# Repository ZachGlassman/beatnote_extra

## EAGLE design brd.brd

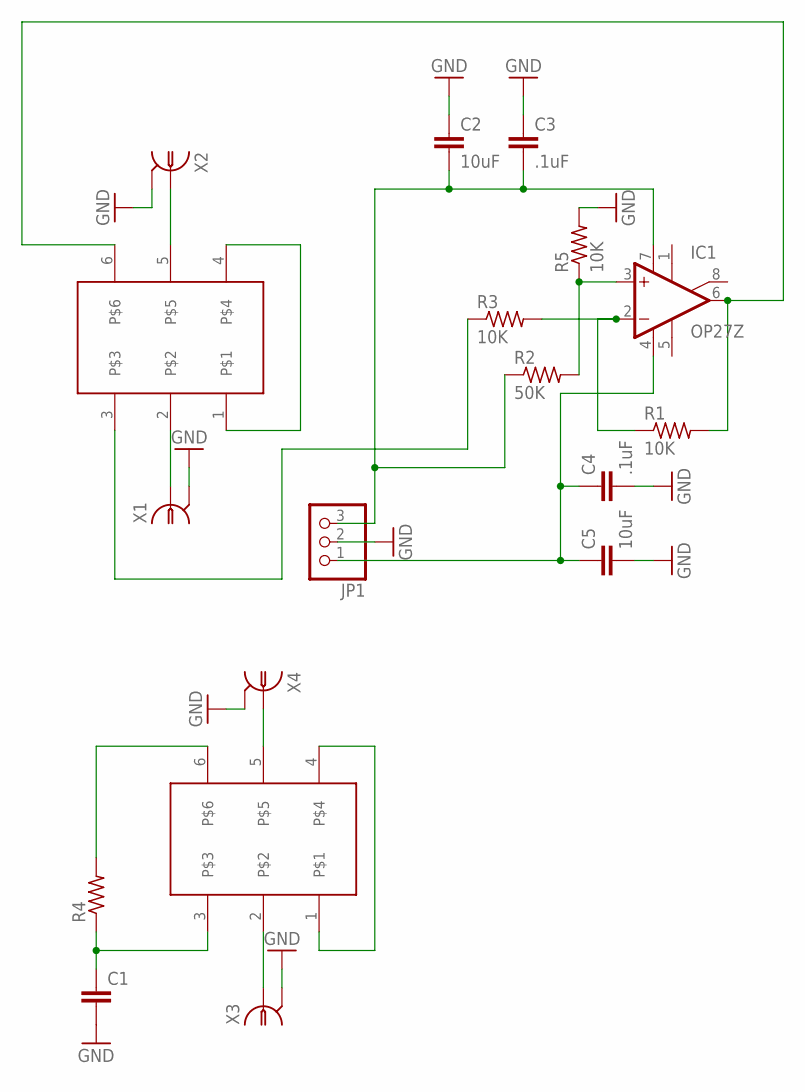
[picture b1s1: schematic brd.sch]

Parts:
C1: C-EU025-024X044; C025-024X044
C2, C5: 10uF; C025-024X044
C3, C4: .1uF; C025-024X044
IC1: OP27Z; DIL08
JP1: PINHD-1X3; 1X03
R1, R3, R5: 10K; 0204V
R2: 50K; 0204V
R4: R-US_0204/2V; 0204V
U$1, U$2: DP3T-TOGGLE; 7201MD9AV2BE
X1, X2, X3, X4: BNC-H; BNC90

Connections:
GND: C1.2, C2.1, C3.1, C4.2, C5.2, JP1.2, R5.2, X1.2, X2.2, X3.2, X4.2
unnamed: IC1.2 (-IN), R1.1, R3.2
unnamed: IC1.6 (OUT), R1.2, U$1.6
unnamed: C4.1, C5.1, IC1.4 (V-), JP1.1
unnamed: U$2.2, X3.1
unnamed: U$2.5, X4.1
unnamed: U$1.2, X1.1
unnamed: C2.2, C3.2, IC1.7 (V+), JP1.3, R2.1
unnamed: C1.1, R4.1, U$2.3
unnamed: IC1.3 (+IN), R2.2, R5.1
unnamed: U$2.1, U$2.4
unnamed: U$1.5, X2.1
unnamed: R3.1, U$1.3
unnamed: U$1.1, U$1.4
unnamed: R4.2, U$2.6

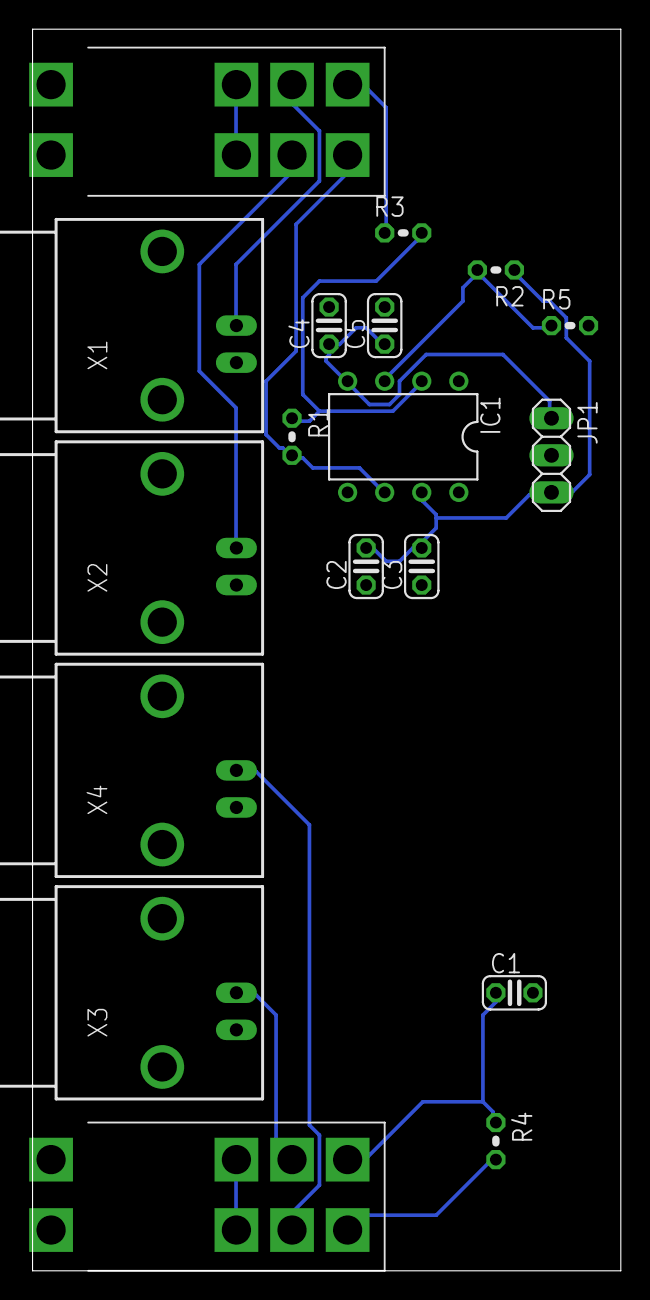
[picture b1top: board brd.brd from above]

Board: 2 copper layers, 40.3 x 85.1 mm, 18 parts (0 on the bottom side), 15 nets.

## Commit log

2017-03-21 better circuit
2017-03-21 added switches
2017-03-21 fixed ordering
